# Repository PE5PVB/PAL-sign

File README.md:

# PAL-sign
Advanced CVBS PAL test card generator, built around an RP2350 and an ADV7391 video encoder

A standalone hardware test card generator for anyone working with analogue television: an ATV contest, aligning a transmitter or receiver, or just needing a proper PAL B/G composite signal on the bench. Twenty-six built-in test cards, generated in real time and sent out as CVBS, no PC required to run it.

<p align="center"><br><i>The assembled board: three buffered composite video outputs on BNC, each with its own 75 ohm driver, USB-C and a DC jack, the ML2032 backup cell of the real-time clock, and the headers for the front panel and the PCM1808 ADC.</i></p>

## Features
- Twenty-six built-in test cards: PM5644 (4:3 and 16:9) and the monochrome PM5644 Indian Head monoscope, BBC Cards F/G/W, FuBK (full, simple and 16:9), EBU colour bars and black & white, the ADV7391's own internal colour bars, Crosshatch, Multiburst, Pulse & Bar, sin(x)/x, Mixed bars, Picdream, a BATC card and the BATC Legacy card of the BBC Micro era, four ATV Contest pages with callsign, contest number, locator and frequency, a TVE card and an analogue TV clock
- Fourteen Custom slots for your own pictures, uploaded from the PC tool
- BBC Test Card F and W can each show a photo of your own instead of the original, centred and uploaded from the PC tool
- Teletext, WSS aspect ratio signalling and Insertion Test Signal (ITS) support
- A slideshow with a fade between pictures
- A scrolling ticker band, colour, speed and size configurable per card
- An on-device menu on its own screen, driven by a rotary encoder, so every setting is reachable without a PC
- Optional PCM audio: with a PCM1808 ADC attached, two extra cards embed stereo sound in the picture itself (see "PCM audio" below)
- A real-time clock with a backup cell on the board (RV-3028-C7 or RV-3032-C7), so date and time survive a power cut; the on-screen clocks follow summer time automatically if you let them
- A Windows configurator to upload your own pictures and change every setting from a PC; it reconnects to the port it used last time

## Controls and settings
Everything below is reachable from the on-device screen and knob, or from the PC tool; the two show the same settings.

### The screen and the knob
A small screen and a rotary encoder on the front, entirely optional: unplug that panel and the firmware skips it and keeps generating video (a pin on the flatcable tells it whether the panel is there). Turning the knob steps through the list of cards without touching what is on air; pushing switches to the highlighted one.
- A short press opens a menu for the card currently shown, with everything specific to that one card.
- A press held for about two seconds opens the System menu instead, with everything that is not tied to one card.
- The menu closes itself after a minute of no input.
- Holding the knob down while powering the board on starts a five-second on-screen countdown; holding through the whole countdown runs a full factory reset (every setting back to its default) once it finishes, releasing early cancels it.

### The per-card menu (short press)
What is offered depends on the card: one with no room for a ticker will not offer one, and one with no clock box will not offer a colour for it. Between them, the cards can offer:
- Enabled: whether stepping through the cards can land on this one; a disabled card keeps its settings, it is just skipped
- Ticker: off, solid or transparent (transparent only on a built-in card, an uploaded photo has no room budget for it), its vertical position, speed and direction, one of five sizes and four fonts, and its colour
- Aspect ratio: nine WSS modes, off, 4:3 full frame, 14:9 letterbox (centred or at the top), 14:9 full frame, 16:9 letterbox (centred or at the top), 16:9 anamorphic, and a wider-than-16:9 letterbox, switching the ADV7391's own wide screen signalling to match
- The first and second identification lines: shown or hidden, and their own colour
- The moving line, on the cards that have one
- The insert boxes (a running clock, or fixed text instead): off, time only, date and time, or the fixed text
- The text font used for all of the above
- A handful of card-specific extras: the PM5644 16:9's chroma test bars, Test Card G's AP2 variant, the ATV Contest pages' three lines (callsign, locator, frequency) and contest number, each of the four pages on its own, BATC Legacy's third text line, and BBC Test Card F/W's own switch for a custom photo instead of the original

### The System menu (long press)
- Text: the first and second identification line, the ticker message, and the fixed text an insert box shows instead of a running clock
- Switches: teletext, ITS (Insertion Test Signal), VBI, and automatic summer time
- Two cycles: the ADV7391's luma and chroma filter presets
- The screen's own brightness
- The date and time, set field by field, kept automatically in step with summer time if that switch is on
- Enabling or disabling any of the cards, without touching what is currently on air
- Seven analogue controls on the ADV7391 itself: DAC gain, Y scale, brightness, hue, the luma peaking filter (SSAF), and the luma and chroma delay

### The slideshow
A sequence of steps, each "how long, which card", built by dragging cards into an order in the PC tool. Any card can appear more than once, each occurrence with its own duration, and there is an optional fade between pictures. The sequence is stored in its own flash page and survives a power cycle, so a slideshow left running keeps running after a restart.

### The ticker
A scrolling text band that can run on almost any card, configured per card as listed above: on or off, or transparent over the picture instead of a solid band; where it sits, how fast and in which direction it scrolls; one of five sizes, one of four fonts, and its own colour. The message itself is shared across every card that shows it.

### Your own photo on BBC Test Card F and W
Both cards have their own oval photo window built in; the PC tool's "Upload portrait..." button lets you put your own picture there instead. The two windows are not quite the same size or shape, so one upload feeds both: choose a photo, drag it and use the zoom slider until the right part sits inside both outlines shown on the preview, and both are cut out and sent in one step. Each card keeps its own on/off switch (see the per-card menu above), so you can show your photo on one, the original on the other, or either everywhere.

## Test cards
Nine of the twenty-six. The first five were captured straight off the composite output; the BATC card, BATC Legacy and the TV clock are frame dumps read back from the board, and the ATV Contest page is drawn from the firmware's own glyph tables, exactly as the board renders it.

<table>
<tr>
<td width="33%"><br><b>PM5644</b><br>The classic Philips PM5644, straight from the original EPROM dump: colour bars, a resolution grating in each corner, a grey scale and the two identification boxes, "PE5PVB" and "CAPELLE" here, with the on-device clock in the middle.</td>
<td width="33%"><br><b>FuBK</b><br>FuBK, the German counterpart of the PM5544, taken from an actual composite recording. The two striped fields right of the gradient bars deliberately mis-modulate the colour signal; a properly working PAL decoder averages them down to plain grey.</td>
<td width="33%"><br><b>PM5644 16:9</b><br>The same PM5644 picture from a newer generation of the encoder EPROM (G924): finer detail and the identification boxes in slightly different places than the plain PM5644.</td>
</tr>
<tr>
<td width="33%"><br><b>BBC Test Card F</b><br>The well known girl-and-clown card, rebuilt from the original photo scan, surrounded by colour bars, resolution wedges and a grey scale.</td>
<td width="33%"><br><b>Mixed bars</b><br>The same eight colour bars twice: once in colour, once with the chroma stripped out, so the bottom row shows exactly the brightness each colour bar carries.</td>
<td width="33%"><br><b>ATV Contest</b><br>Callsign, contest number, locator and working frequency in large, legible digits, meant to be read off a weak or noisy signal during a contest. There are four of these pages, each with its own texts and number, so a station can switch between contests or bands with one click of the knob; the frequency line uses a smaller face so that a 10 GHz frequency fits in full.</td>
</tr>
<tr>
<td width="33%"><br><b>BATC card</b><br>Laid out after a BATC repeater card: a frequency staircase on top, seven rows of ever finer bars down to a 4 MHz square wave, the callsign large beside colour bars, and reversed bars with a grey staircase below.</td>
<td width="33%"><br><b>BATC Legacy</b><br>The amateur television test card of the BBC Micro era, after the G7GTN version of the BATC book's "Test Card with Call sign": the callsign large, with two text lines under the colour bars, the lower one its own setting.</td>
<td width="33%"><br><b>TV clock</b><br>A full-picture analogue clock after the TV Klok of depips.nl, with the second hand stepping once a second, driven by the board's real-time clock; the identification lines sit in the corner.</td>
</tr>
</table>

## How it works

### From pixels to composite video
The RP2350 does not generate the analogue PAL signal itself. Its PIO hardware (a handful of small, exactly timed state machines built into the chip for jobs like this) pushes the picture out as a digital YCbCr 4:2:2 byte stream on an 8 bit bus, together with a 27 MHz clock, following the BT.656 standard. That digital stream, plus a couple of control pins, goes straight into an Analog Devices ADV7391 video encoder over I2C for configuration. The ADV7391 does the actual PAL encoding: it generates the colour subcarrier, mixes in luma and chroma, adds the analogue sync pulses and drives the composite (CVBS) output.

### No separate sync wires
An older-style video source uses two extra wires next to the picture data, HSYNC and VSYNC, to mark the start of every line and every field. BT.656 does not need them: it puts special byte codes (SAV and EAV, values that never occur in real picture data) straight into the byte stream itself, at the start and end of every active line. The ADV7391 reads its own timing out of those codes, so on this board HSYNC and VSYNC are simply wired high and never toggle.

### Keeping the two cores in step
One RP2350 core works out the pixel data for the current picture, line by line, and writes it into a ring buffer. The other core only reads that buffer back out to the PIO/DMA hardware, at a fixed pace, so the picture can never fall behind: DMA moves the bytes from the buffer into the PIO's FIFO without either core handling them one by one. If the rendering core ever gets too far behind, for instance during a picture switch, the firmware notices and falls back to repeating the last complete picture instead of letting anything incomplete reach the screen.

### Teletext, WSS and the other things hidden in the picture
Teletext, the widescreen signalling (WSS) and the insertion test signal (ITS) are not produced by a separate chip. They are ordinary picture data: a handful of lines in the vertical blanking interval, the lines you never actually see, above and below the visible picture, get filled with luma samples that decode into the teletext bits or the WSS code, exactly like any other line of picture content decodes into a colour. The firmware works out that waveform itself, pulse by pulse, to the shape the relevant standard requires, and writes it straight into the same buffer the ADV7391 streams out.

### Test cards and your own pictures
The twenty-six built-in test cards are pixel data compiled straight into the firmware; several of them, the PM5644 and BBC cards, come from the original EPROM dumps of real broadcast test card generators. Alongside those sit fourteen Custom slots: plain picture data reserved in the last part of the 16 MB flash chip, which you fill from the PC tool over the same USB serial connection used for firmware uploads.

### The clock
The clocks in the picture, the PM5644's centre box, the TV clock and the date and time inserts, run on a real-time clock chip on the board, a Micro Crystal RV-3028-C7 or, on the newer board variant, an RV-3032-C7; the firmware looks for both at power-on and drives whichever it finds. A rechargeable ML2032 cell keeps that chip running through a power cut, trickle charged from the board's own supply, so the time only has to be set once, from the menu or the PC tool. A board without either chip still keeps time while it is powered, but starts from a fixed default date at every power-on until the time is set again.

### The screen and the knob
The screen on the front is a plain SPI display, and the knob next to it is an ordinary quadrature rotary encoder, decoded from a GPIO interrupt so a fast turn is never missed; see "Controls and settings" above for what they do.

## Connecting the screen and the knob
The screen and the rotary encoder live on their own small front panel PCB, connected with a flatcable, and the whole panel is optional: one pin on the cable tells the firmware whether it is there, and without it the board runs headless and keeps generating video.

The display is an **ST7789P3** SPI panel of **76 x 284 pixels** (a window inside the controller's 240 x 320 frame memory), driven over SPI0. The knob is an ordinary quadrature rotary encoder with a push switch; the RP2350's internal pull-ups do the rest, so the panel needs no resistors or capacitors of its own.

| Signal | GPIO | Notes |
|---|---|---|
| Display RST | GP19 | |
| Display CS | GP20 | |
| Display DC | GP21 | low = command |
| Display SCK | GP22 | SPI0 SCK |
| Display MOSI (SDA) | GP23 | SPI0 TX |
| Display backlight | GP26 | active high |
| Panel present | GP24 | tie to GND on the panel |
| Encoder phase A | GP27 | internal pull-up |
| Encoder phase B | GP28 | internal pull-up |
| Encoder push | GP29 | internal pull-up |

Plus 3.3 V and GND for the panel itself. The encoder's common and the switch's other side go to GND.

## PCM audio
An optional PCM1808 audio ADC turns the generator into a video-plus-audio source: the analogue stereo input is sampled at 48 kHz and embedded in the picture itself as data lines, in the spirit of the PCM adaptors of the early digital audio era. Two extra cards carry it:

- **Ham PCM**: an own format designed for FM ATV links, with Reed-Solomon error protection, a small text channel, and four quality modes: HQ (48 kHz, 14 bit stereo), LQ (32 kHz, 12 bit stereo), Voice (32 kHz A-law) and Narrow (16 kHz mono A-law).
- **Sony PCM**: a Sony/EIAJ STC-007-compatible signal (44.1 kHz, 14 or 16 bit, selectable pre-emphasis) that period PCM adaptors and third-party software decoders understand.

Both cards appear automatically when the ADC is detected at power-on, and stay completely hidden without it, on the board, in the menu and in the PC tool alike. The `PcmDecoder` tool in `PC Software/` plays the audio back on a PC from a composite capture card, with a live view of the decode quality.

The ADC connects over I2S, with the PCM1808 in master mode: the board supplies only the 12.288 MHz system clock, and the ADC generates its own bit and word clocks from it.

| Signal | GPIO | Direction |
|---|---|---|
| SCKI (256 fs master clock) | GP13 | board to ADC |
| BCK (bit clock) | GP9 | ADC to board |
| LRCK (word clock) | GP10 | ADC to board |
| DOUT (I2S data) | GP11 | ADC to board |

Plus supply and GND for the ADC board. The PCM1808's mode pins go high for master mode (MD1 = MD0 = high).

## Repository layout
- `Firmware/` -- the firmware for the RP2350, built with PlatformIO or the Arduino IDE
- `PC Software/` -- the Windows configurator and the PCM decoder, see [the configurator's README](PC%20Software/Configurator/README.md) for how to build it
- `Hardware/RV-3028-C7 version/` -- the KiCad project of the board, with the schematic as PDF and the fabrication output (Gerbers, BOM, positions)
- `Hardware/RV-3032-C7 version/` -- the same board with the RV-3032-C7 as its real-time clock, for when the RV-3028-C7 is hard to get
- `Hardware/Gerbers/` -- the fabrication output of the RV-3028-C7 board on its own

## Building the firmware
```
cd Firmware
pio run
pio run -t upload
```
PlatformIO picks up everything it needs from `platformio.ini`, including the board profile for the bare RP2350. Opening `Firmware.ino` in the Arduino IDE (2.x) works as well; `sketch.yaml` carries the same board settings.

## Contributing
Found a bug or have an idea? Open an [issue](https://github.com/PE5PVB/PAL-sign/issues) or a [pull request](https://github.com/PE5PVB/PAL-sign/pulls), I will review it and merge into main. Since this project is dual-licensed (see below), a pull request means you agree that your contribution is licensed the same way as the rest of the project, under both the GPLv3 and the commercial license.

## License
This project is dual-licensed.

You may use it under the terms of the GNU General Public License, either version 3 of the License, or (at your option) any later version: this program is free software, you can redistribute it and/or modify it under those terms. It is distributed in the hope that it will be useful, but WITHOUT ANY WARRANTY; without even the implied warranty of MERCHANTABILITY or FITNESS FOR A PARTICULAR PURPOSE. See the [LICENSE](LICENSE) file for the full text.

If the GPLv3's terms do not suit your use, for example because you want to use this project, or a part of it, in a closed-source or commercial product without releasing your own source code, a separate commercial license is available. See [pe5pvb.nl](https://www.pe5pvb.nl/) for contact details.

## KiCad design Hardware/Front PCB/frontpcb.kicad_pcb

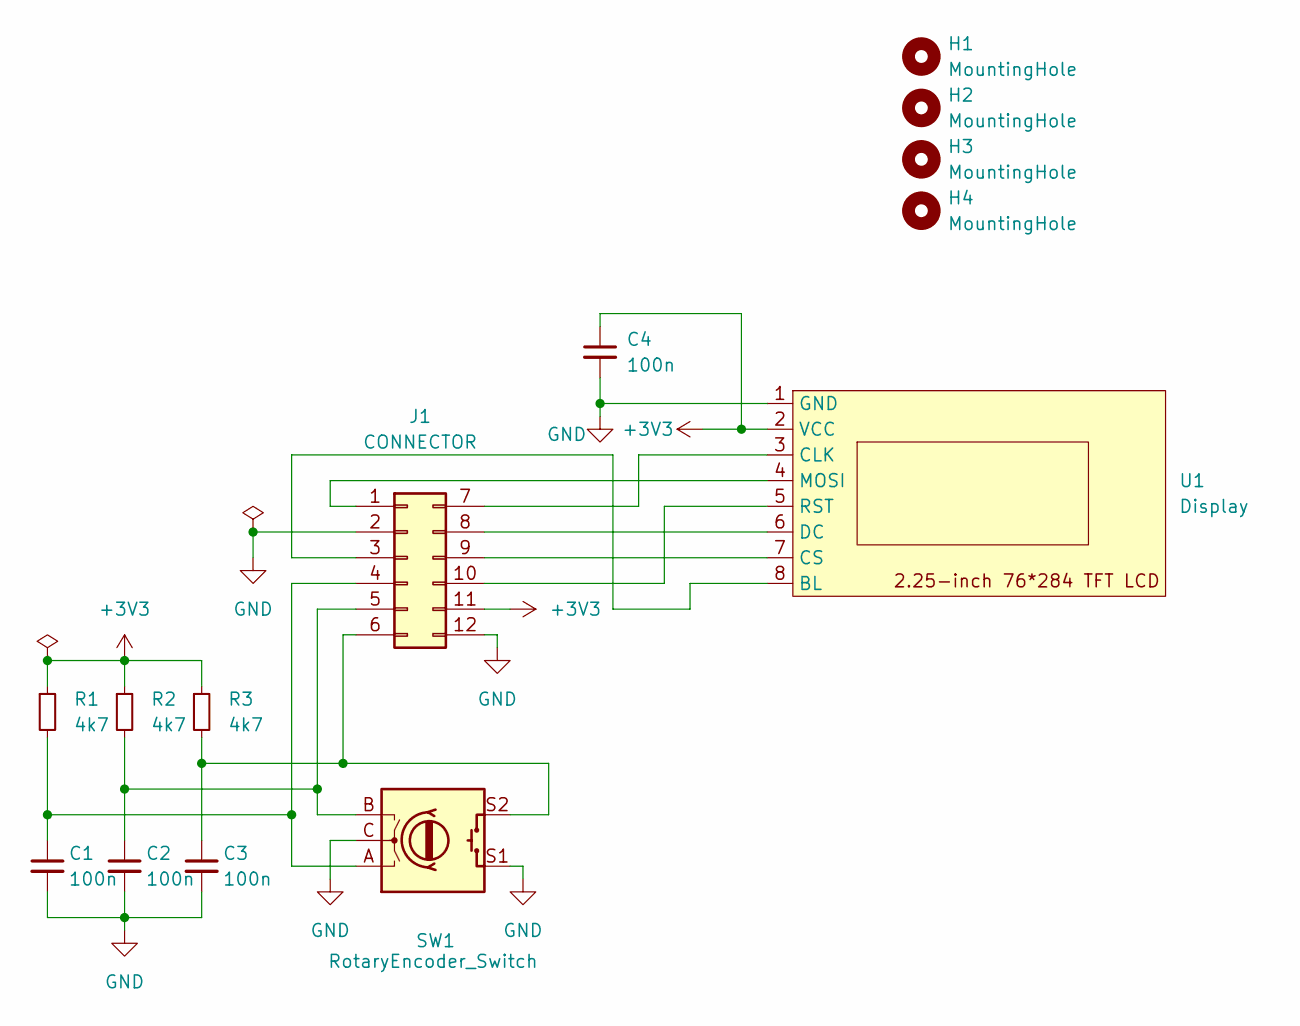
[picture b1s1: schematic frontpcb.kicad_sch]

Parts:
C1, C2, C3, C4: 100n; C_0603_1608Metric
H1, H2, H3, H4: MountingHole; MountingHole_3.2mm_M3
J1: CONNECTOR; PinHeader_2x06_P2.54mm_Vertical
R1, R2, R3: 4k7; R_0603_1608Metric
SW1: RotaryEncoder_Switch; RotaryEncoder_Alps_EC11E-Switch_Vertical_H20mm
U1: Display; 2.25-inch 76_284 TFT LCD

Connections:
+3V3: C4.1, J1.11, R1.1, R2.1, R3.1, U1.2 (VCC)
GND: C1.2, C2.2, C3.2, C4.2, J1.2, J1.12, SW1.C, SW1.S1, U1.1 (GND)
unnamed: J1.1, U1.4 (MOSI)
unnamed: J1.3, U1.8 (BL)
unnamed: C1.1, J1.4, R1.2, SW1.A
unnamed: C2.1, J1.5, R2.2, SW1.B
unnamed: C3.1, J1.6, R3.2, SW1.S2
unnamed: J1.7, U1.3 (CLK)
unnamed: J1.8, U1.6 (DC)
unnamed: J1.9, U1.7 (CS)
unnamed: J1.10, U1.5 (RST)

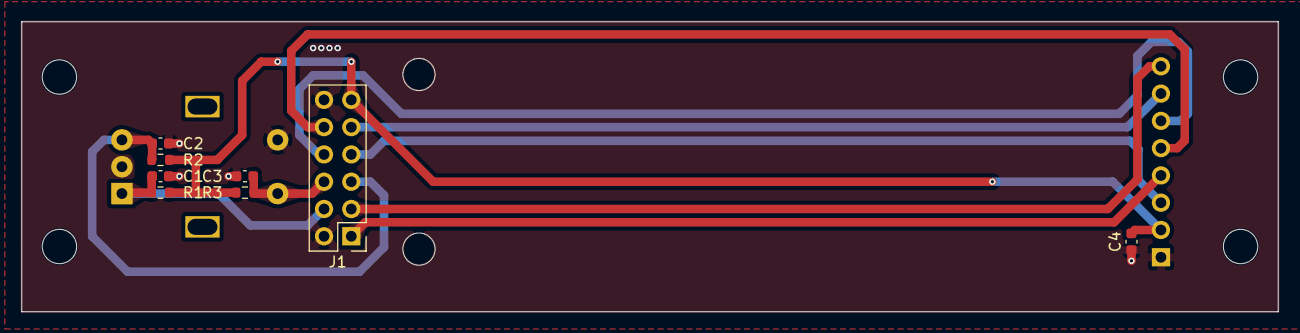
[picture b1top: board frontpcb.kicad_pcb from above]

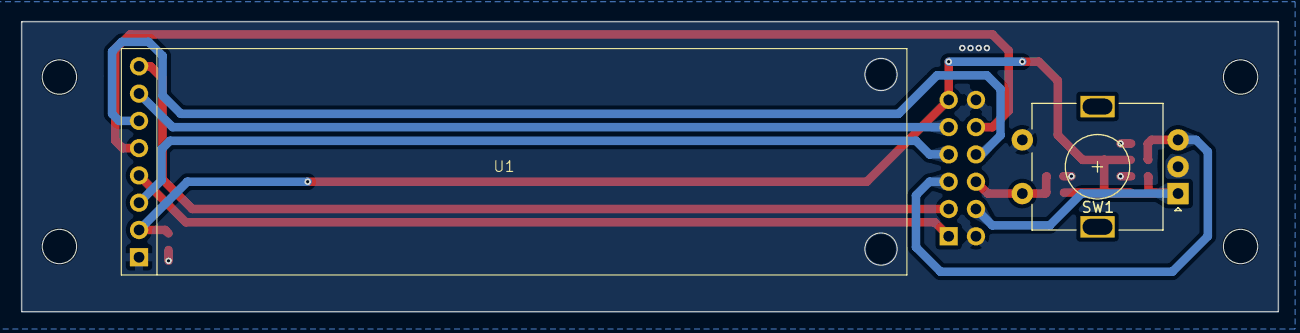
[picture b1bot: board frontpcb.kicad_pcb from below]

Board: 2 copper layers, 117.0 x 27.0 mm, 14 parts (2 on the bottom side), 11 nets.

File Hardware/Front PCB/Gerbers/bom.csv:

Designator,Footprint,Quantity,Value,LCSC Part #
"C1, C2, C3, C4",0603,4,100n,
J1,PinHeader_2x06_P2.54mm_Vertical,1,CONNECTOR,
"R1, R2, R3",0603,3,4k7,
SW1,RotaryEncoder_Alps_EC11E-Switch_Vertical_H20mm,1,RotaryEncoder_Switch,
U1,2.25-inch 76_284 TFT LCD,1,Display,

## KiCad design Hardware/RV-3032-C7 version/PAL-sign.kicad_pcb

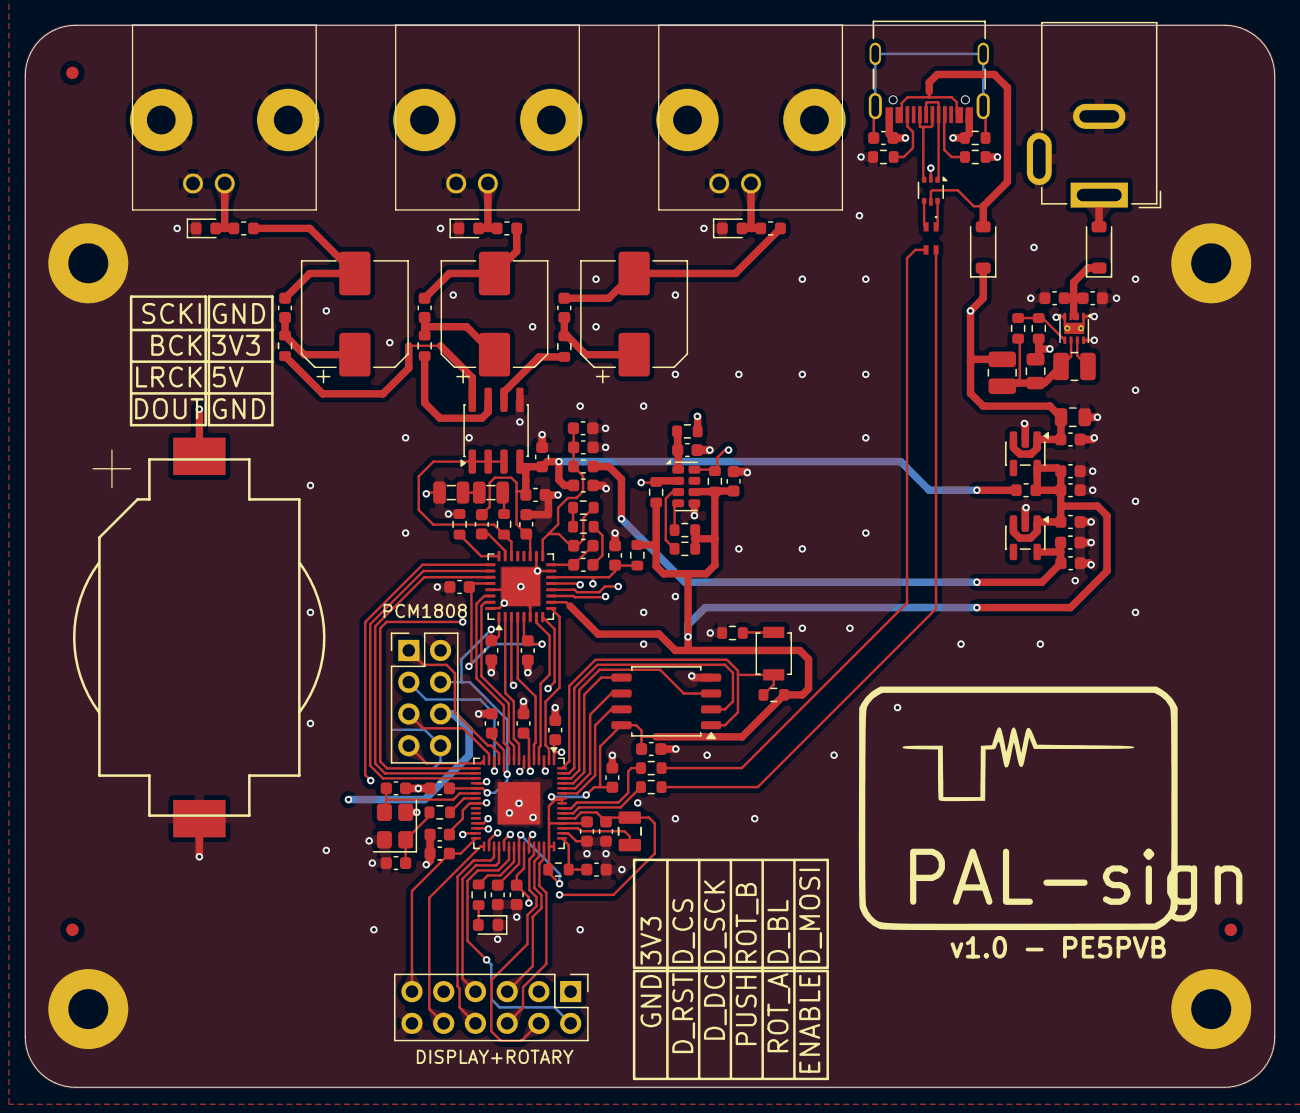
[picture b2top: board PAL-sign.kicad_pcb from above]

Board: 4 copper layers, 100.0 x 85.0 mm, 115 parts (0 on the bottom side), 91 nets.

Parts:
BT1: ML2032; CR2032-BS-6-1
C1, C2, C5, C6, C9: 4.7uF; C_0603_1608Metric
C3, C4: 15p; C_0603_1608Metric
C7, C8, C10, C12, C13, C14, C15, C16, C17, C18, C19, C20, C21, C22, C25, C28, C32, C34, C35, C37, C39, C42, C44, C45, C47: 100n; C_0603_1608Metric
C11: 4n7; C_0603_1608Metric
C23, C38, C43, C46: 10uF; C_0603_1608Metric
C24, C27: 10n; C_0603_1608Metric
C26: 2.2nF; C_0603_1608Metric
C29: 150n; C_0603_1608Metric
C30: 12n; C_0603_1608Metric
C31, C33, C36: 470uF; CP_Elec_8x10
C40, C41: 22uF; C_0805_2012Metric
D1, D6: B5819W; D_SOD-123
D2: ACT; LED_0603_1608Metric
D3, D4, D5: CG0603MLC-05LE; D_0603_1608Metric
FB1, FB5: BLM18HG601SN1D; L_0603_1608Metric
FB2, FB3, FB4: BLM18PG331SN1D; L_0603_1608Metric
FID1, FID2, FID3: Fiducial; Fiducial_1mm_Mask2mm
H1, H2, H3, H4: M3; MountingHole_3.2mm_M3_Pad
J1: 12402012E212A
J2: I2S; PinHeader_2x04_P2.54mm_Vertical
J3: FRONT; PinHeader_2x06_P2.54mm_Vertical
J4: VIDEO1; RF1-01A-D-00-75-M
J5: VIDEO2; RF1-01A-D-00-75-M
J6: VIDEO3; RF1-01A-D-00-75-M
J7: Barrel_Jack_Switch; BarrelJack_GCT_DCJ200-10-A_Horizontal
L1: 3.3uH; L_0806_2016Metric
L2: ACM2012-201-2P-T001; FIL_ACM2012-900-2P-T002
L3: 4.7uH; L_0805_2012Metric_2
L4: 1.5uH; L_0805_2012Metric_2
L5, L6: 2.2uH; L_1008_2520Metric
R1, R16, R18: 10k; R_0603_1608Metric
R2: 33; R_0603_1608Metric
R3, R4, R25: 1k; R_0603_1608Metric
R5, R6: 27.4; R_0603_1608Metric
R7: 1M; R_0603_1608Metric
R8: 2k2; R_0603_1608Metric
R9, R10, R11, R12, R13: 5k1; R_0603_1608Metric
R14: 4k12; R_0603_1608Metric
R15: 300; R_0603_1608Metric
R17: 150; R_0603_1608Metric
R19: 20; R_0603_1608Metric
R20, R21, R22: 75; R_0603_1608Metric
R23: 1M1; R_0603_1608Metric
R24: 210k; R_0603_1608Metric
SW1: BOOT; SW_SPST_B3U-1000P
U1: W25Q128JVS; SOIC-8_5.3x5.3mm_P1.27mm
U2: USBLC6-2P6; SOT-666
U3: RP2350A; QFN-60-1EP_7x7mm_P0.4mm_EP3.4x3.4mm
U4: ADV7391BCPZ; LFCSP-32-1EP_5x5mm_P0.5mm_EP3.1x3.1mm
U5: RV-3032-C7; MicroCrystal_C7_SON-8_1.5x3.2mm_P0.9mm
U6: THS7314; SOIC-8_3.9x4.9mm_P1.27mm
U7: TPS62160DSG; Texas_DSG0008A_WSON-8-1EP_2x2mm_P0.5mm_EP0.9x1.6mm_ThermalV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
U8: TPS7A2033PDBVR; SOT-23-5
U9: TPS7A2018PDBVR; SOT-23-5
Y1: ABM8-272-T3; Crystal_SMD_3225-4Pin_3.2x2.5mm

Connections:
+1V8: C18.1, C20.1, C46.1, C47.1, FB1.1, U4.5 (V_{DD}), U4.28 (V_{DD}), U9.5 (OUT)
+3.3VA: C23.1, C25.1, C26.1, C27.1, C28.1, FB5.2, U4.19 (V_{AA}), U6.4 (Vs+)
+3V3: C2.1, C5.1, C10.1, C12.1, C13.1, C14.1, C15.1, C16.1, C19.1, C35.1, C43.1, C44.1, C45.1, FB5.1, J2.4, J3.11, R1.1, R2.1, R11.2, R12.2, R13.2, R16.1, R18.1, U1.8 (VCC), U3.1 (IOVDD), U3.11 (IOVDD), U3.20 (IOVDD), U3.30 (IOVDD), U3.38 (IOVDD), U3.44 (ADC_AVDD), U3.45 (IOVDD), U3.49 (VREG_VIN), U3.53 (USB_OTP_VDD), U3.54 (QSPI_IOVDD), U4.1 (V_{DD_IO}), U4.10 (ALSB), U5.6 (VDD), U8.5 (OUT), U9.1 (IN), U9.3 (EN)
+5V: C41.1, C42.1, D1.1 (K), J2.6, L6.2, U8.1 (IN), U8.3 (EN)
GND: BT1.2 (-), C1.2, C2.2, C3.2, C4.2, C5.2, C6.2, C7.2, C8.2, C9.2, C10.2, C11.1, C12.2, C13.2, C14.2, C15.2, C16.2, C17.2, C18.2, C19.2, C20.2, C21.2, C22.2, C23.2, C24.2, C25.2, C27.2, C28.2, C35.2, C38.2, C39.2, C40.2, C41.2, C42.2, C43.2, C44.2, C45.2, C46.2, C47.2, D2.1 (K), D3.1 (A1), D4.1 (A1), D5.1 (A1), H1.1 (1_1), H2.1 (1_1), H3.1 (1_1), H4.1 (1_1), J1.A1 (GND_A), J1.B1 (GND_B), J2.2, J2.8, J3.12, J4.2 (Ext), J5.2 (Ext), J6.2 (Ext), J7.2, J7.3, L4.2, R4.2, R7.1, R9.2, R10.2, R14.2, R24.2, U1.4 (GND), U2.2 (GND), U3.47 (VREG_PGND), U3.61 (GND), U4.6 (DGND), U4.15 (PGND), U4.18 (AGND), U4.29 (DGND), U4.32 (GND_IO), U4.33 (AGND), U5.5 (VSS), U6.5 (GND), U7.1 (PGND), U7.4 (AGND), U7.8 (PG), U7.9 (PAD), U8.2 (GND), U9.2 (GND), Y1.2 (G), Y1.4 (G)
unnamed: BT1.1 (+), R25.1
unnamed: C4.1, R3.1, Y1.1
unnamed: C11.2, J1.S1 (SHIELD), J1.S2 (SHIELD), J1.S3 (SHIELD), J1.S4 (SHIELD), R7.2
unnamed: C29.2, R17.1
unnamed: C31.1, C32.1, R20.1
unnamed: C31.2, C32.2, FB2.1
unnamed: C33.1, C34.1, R22.1
unnamed: C33.2, C34.2, FB3.1
unnamed: C36.1, C37.1, R21.2
unnamed: C36.2, C37.2, FB4.1
unnamed: D1.2 (A), J1.A4 (VBUS_A), J1.B4 (VBUS_B), U2.5 (VBUS)
unnamed: D2.2 (A), R8.2
unnamed: D3.2 (A2), FB2.2, J4.1 (In)
unnamed: D4.2 (A2), FB3.2, J5.1 (In)
unnamed: D5.2 (A2), FB4.2, J6.1 (In)
unnamed: D6.2 (A), J7.1
unnamed: C38.1, C39.1, D6.1 (K), U7.2 (VIN), U7.3 (EN)
unnamed: J1.A5 (CC1), R10.1
unnamed: J1.B5 (CC2), R9.1
unnamed: J1.A6 (D1+), J1.B6 (D2+), U2.3 (I/O2)
unnamed: J1.A7 (D1-), J1.B7 (D2-), U2.1 (I/O1)
unnamed: J2.1, U3.12 (GPIO8)
unnamed: J2.3, U3.13 (GPIO9)
unnamed: J2.5, U3.14 (GPIO10)
unnamed: J2.7, U3.15 (GPIO11)
unnamed: J3.1, U3.35 (GPIO23)
unnamed: J3.2, U3.36 (GPIO24)
unnamed: J3.3, U3.40 (GPIO26/ADC0)
unnamed: J3.4, U3.41 (GPIO27/ADC1)
unnamed: J3.5, U3.42 (GPIO28/ADC2)
unnamed: J3.6, U3.43 (GPIO29/ADC3)
unnamed: J3.7, U3.34 (GPIO22)
unnamed: J3.8, U3.33 (GPIO21)
unnamed: J3.9, U3.32 (GPIO20)
unnamed: J3.10, U3.31 (GPIO19)
unnamed: L2.1, U2.6 (I/O1)
unnamed: L2.2, R5.1
unnamed: L2.3, U2.4 (I/O2)
unnamed: L2.4, R6.1
unnamed: L3.1, R15.2
unnamed: L3.2, L4.1
unnamed: R4.1, SW1.1
unnamed: R17.2, R19.2
unnamed: U1.6 (CLK), U3.56 (QSPI_SCLK)
unnamed: U1.5 (DI/IO_{0}), U3.57 (QSPI_SD0)
unnamed: U1.2 (DO/IO_{1}), U3.59 (QSPI_SD1)
unnamed: R1.2, SW1.2, U1.1 (~CS), U3.60 (~QSPI_SS)
unnamed: U1.7 (~HOLD/~RESET/IO_{3}), U3.55 (QSPI_SD3)
unnamed: U1.3 (~WP/IO_{2}), U3.58 (QSPI_SD2)
unnamed: U3.2 (GPIO0), U4.9 (P7)
unnamed: U3.3 (GPIO1), U4.8 (P6)
unnamed: U3.4 (GPIO2), U4.7 (P5)
unnamed: U3.5 (GPIO3), U4.4
unnamed: U3.7 (GPIO4), U4.3
unnamed: U3.8 (GPIO5), U4.2
unnamed: U3.9 (GPIO6), U4.31 (P1)
unnamed: U3.10 (GPIO7), U4.30 (P0)
unnamed: U3.16 (GPIO12), U4.13 (CLKIN)
unnamed: U3.17 (GPIO13), U4.27 (~HSYNC)
unnamed: U3.18 (GPIO14), U4.26 (~VSYNC)
unnamed: C17.1, R11.1, U3.19 (GPIO15), U4.14 (~RESET)
unnamed: R13.1, U3.27 (GPIO16), U4.11 (SDA), U5.2 (SDA)
unnamed: R12.1, U3.28 (GPIO17), U4.12 (SCL), U5.8 (SCL)
unnamed: U3.29 (GPIO18), U4.25 (SFL)
unnamed: R8.1, U3.37 (GPIO25)
unnamed: R5.2, U3.51 (USB_DM)
unnamed: R6.2, U3.52 (USB_DP)
unnamed: C6.1, R2.2, U3.46 (VREG_AVDD)
unnamed: C1.1, C7.1, C8.1, C9.1, L1.1, U3.6 (DVDD), U3.23 (DVDD), U3.39 (DVDD), U3.50 (VREG_FB)
unnamed: L1.2, U3.48 (VREG_LX)
unnamed: C3.1, U3.21 (XIN), Y1.3
unnamed: R3.2, U3.22 (XOUT)
unnamed: C26.2, U4.23 (COMP)
unnamed: R15.1, U4.22 (DAC1), U6.1 (CH1IN), U6.2 (CH2IN), U6.3 (CH3IN)
unnamed: C29.1, C30.1, U4.16 (EXT_LF)
unnamed: C22.1, C24.1, C30.2, FB1.2, R19.1, U4.17 (P_{VDD})
unnamed: R14.1, U4.24 (R_{SET})
unnamed: R18.2, U5.4 (EVI)
unnamed: C21.1, R25.2, U5.1 (VBACKUP)
unnamed: R16.2, U5.3 (~INT)
unnamed: R20.2, U6.8 (CH1OUT)
unnamed: R22.2, U6.7 (CH2OUT)
unnamed: R21.1, U6.6 (CH3OUT)
unnamed: R23.2, R24.1, U7.5 (FB)
unnamed: L5.1, U7.7 (SW)
unnamed: C40.1, L5.2, L6.1, R23.1, U7.6 (VOS)

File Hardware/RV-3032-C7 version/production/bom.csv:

Designator,Footprint,Quantity,Value,LCSC Part #
BT1,CR2032-BS-6-1,1,ML2032,C70377
"C1, C2, C5, C6, C9",0603,5,4.7uF,C19666
"C10, C12, C13, C14, C15, C16, C17, C18, C19, C20, C21, C22, C25, C28, C32, C34, C35, C37, C39, C42, C44, C45, C47, C7, C8",0603,25,100n,C14663
C11,0603,1,4n7,C53987
"C23, C38, C43, C46",0603,4,10uF,C96446
"C24, C27",0603,2,10n, C57112
C26,0603,1,2.2nF,C1604
C29,0603,1,150n,C513735
"C3, C4",0603,2,15p,C1644
C30,0603,1,12n,C107074
"C31, C33, C36",CP_Elec_8x10,3,470uF,C48970894
"C40, C41",0805,2,22uF,C45783
"D1, D6",D_SOD-123,2,B5819W,C8598
D2,0603,1,ACT,C2286
"D3, D4, D5",0603,3,CG0603MLC-05LE,C2655331
"FB1, FB5",0603,2,BLM18HG601SN1D, C85830
"FB2, FB3, FB4",0603,3,BLM18PG331SN1D,C79913
J1,12402012E212A,1,12402012E212A, C5150972
J2,PinHeader_2x04_P2.54mm_Vertical,1,I2S,C5156676
J3,PinHeader_2x06_P2.54mm_Vertical,1,FRONT, C5224012
J4,RF1-01A-D-00-75-M,1,VIDEO1,C5454776
J5,RF1-01A-D-00-75-M,1,VIDEO2,C5454776
J6,RF1-01A-D-00-75-M,1,VIDEO3,C5454776
J7,BarrelJack_GCT_DCJ200-10-A_Horizontal,1,Barrel_Jack_Switch,C16214
L1,0806,1,3.3uH,C42411119
L2,FIL_ACM2012-900-2P-T002,1,ACM2012-201-2P-T001,C383338
L3,0805,1,4.7uH, C6377184
L4,0805,1,1.5uH,C6776060
"L5, L6",1008,2,2.2uH,C576403
"R1, R16, R18",0603,3,10k,C25804
"R10, R11, R12, R13, R9",0603,5,5k1,C23162
R14,0603,1,4k12, C863836
R15,0603,1,300,C23025
R17,0603,1,150,C22808
R19,0603,1,20, C22950
R2,0603,1,33,C23140
"R20, R21, R22",0603,3,75,C4275
R23,0603,1,1M1, C2930138
R24,0603,1,210k,C22952
"R25, R3, R4",0603,3,1k,C21190
"R5, R6",0603,2,27.4, C177713
R7,0603,1,1M, C22935
R8,0603,1,2k2,C4190
SW1,SW_SPST_B3U-1000P,1,BOOT, C231329
U1,SOIC-8_5.3x5.3mm_P1.27mm,1,W25Q128JVS,C97521
U2,SOT-666,1,USBLC6-2P6, C15999
U3,QFN-60-1EP_7x7mm_P0.4mm_EP3.4x3.4mm,1,RP2350A,C42411118
U4,LFCSP-32-1EP_5x5mm_P0.5mm_EP3.1x3.1mm,1,ADV7391BCPZ,C662283
U5,MicroCrystal_C7_SON-8_1.5x3.2mm_P0.9mm,1,RV-3032-C7,C5127802
U6,SOIC-8_3.9x4.9mm_P1.27mm,1,THS7314,C882751
U7,Texas_DSG0008A_WSON-8-1EP_2x2mm_P0.5mm_EP0.9x1.6mm_ThermalVias,1,TPS62160DSG,C324077
U8,SOT-23-5,1,TPS7A2033PDBVR,C2862740
U9,SOT-23-5,1,TPS7A2018PDBVR,C963430
Y1,Crystal_SMD_3225-4Pin_3.2x2.5mm,1,ABM8-272-T3,C20625731

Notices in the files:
README.md:
https://img.shields.io/badge/license%20-%20GNU_GPLv3-GPLv3?color=blue
parts and their libraries:
License: Apache-2.0
